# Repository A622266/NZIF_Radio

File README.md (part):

# NZIF Radio

Near-zero-IF radio architecture built around an 8-phase harmonic rejection polyphase mixer and audio-rate ADC/DAC signal processing.

This board is the NZIF core: it converts differential RF into low-frequency quadrature baseband, then digitizes and processes the result with audio-rate converters and a SigmaDSP. The RF front-end board handles the PA, T/R switch, a band-switched quasi-elliptic LPF bank shared between TX and RX, a directional coupler for SWR and power measurement at the antenna port, and two receive-path high-pass filters that together form a band-specific preselector. The receive and transmit mixer/baseband cores are on this board.

## Design goals

- Suppress the 3rd, 5th, and 7th LO harmonics with an 8-phase harmonic rejection mixer, reducing reliance on RF bandpass filters on this board.
- Use polyphase mixing and phase-domain harmonic suppression to minimize analog RF selectivity requirements.
- Avoid a conventional high-IF architecture: the design is near-zero-IF, using 192 kHz ADC/DAC sampling with a digital NCO offset to stay away from DC and 1/f noise.
- Keep the Rx and Tx front end compact and fully differential, while placing the PA and post-PA filters on a separate board.
- Preserve differential signal flow from the RF mixer through the driver amps and into the audio-rate converters.
- Share a quasi-elliptic post-PA LPF bank between TX and RX on the RF front-end board: on transmit it suppresses PA harmonics for regulatory compliance; on receive the same bank acts as a band-specific preselector with deep notch traps at adjacent-band interference sources.
- Place a directional coupler at the antenna interface (after the LPF bank) for accurate forward/reflected power and SWR measurement at the clean fundamental; use a calibration tap to inject a spectrally clean reference tone into the receive path for I/Q calibration.
- Apply strategically placed high-pass filters in the receive chain: a fixed ~1.6 MHz filter to block AM broadcast on all bands, and a switched ~9 MHz filter to suppress lower-band interference on 30m and above.

## Architecture overview

### Core concept

The NZIF board uses an 8-phase commutating mixer topology on receive and transmit. In the receive path, differential RF (`RF+`, `RF-`) is sampled by eight phase-shifted switch networks, producing eight baseband phase taps. Opposite phases are then recombined into four differential channels for ADC conversion:

- `BB_0` / `BB_180` → `P0_IN+` / `P0_IN-`
- `BB_45` / `BB_225` → `P45_IN+` / `P45_IN-`
- `BB_90` / `BB_270` → `P90_IN+` / `P90_IN-`
- `BB_135` / `BB_315` → `P135_IN+` / `P135_IN-`

The eight-phase approach provides phase-domain cancellation of odd-order LO harmonics (3rd, 5th, 7th) and reduces the need for RF bandpass filtering on this board.

### Near-zero-IF operation

This is not a classic zero-IF design:

- ADC and DAC converters run at 192 kHz.
- The ADAU1467 DSP uses a digital NCO to shift the effective center frequency away from DC.
- That offset avoids LO leakage and 1/f noise while preserving complex I/Q demodulation.

Because the converters are audio-rate, the RF conversion chain moves entirely into the phase-domain mixer and the digital domain — there is no IF filter bank.

## How the receive signal flows

```
Antenna → Directional coupler (~0.2 dB through) → ZWAS LPF bank (band-switched preselector)
    → T/R switch → HP-1 (~1.6 MHz, fixed) → HP-2 (~9 MHz, switched 30m+)
    → SMA (J101) → 1:1 balun → RF+ / RF-
    → SN74CBT3125C quad switch arrays (×4)
        controlled by phase_0, phase_45, … phase_315
        ├─ BB_0    → ADA4625-2 unity-gain buffer
        ├─ BB_45   → ADA4625-2 unity-gain buffer
        ├─ BB_90   → ADA4625-2 unity-gain buffer
        ├─ BB_135  → ADA4625-2 unity-gain buffer
        ├─ BB_180  → ADA4625-2 unity-gain buffer
        ├─ BB_225  → ADA4625-2 unity-gain buffer
        ├─ BB_270  → ADA4625-2 unity-gain buffer
        └─ BB_315  → ADA4625-2 unity-gain buffer
    → top sheet pairs opposite phases into differential channels:
        BB_0/BB_180   → P0_IN+/P0_IN-
        BB_45/BB_225  → P45_IN+/P45_IN-
        BB_90/BB_270  → P90_IN+/P90_IN-
        BB_135/BB_315 → P135_IN+/P135_IN-
    → ADA4945-1 fully differential amplifiers (×4)
        → P0_FDA+/P0_FDA-, P45_FDA+/P45_FDA-,
          P90_FDA+/P90_FDA-, P135_FDA+/P135_FDA-
    → ADAU1979 4-channel 24-bit ADC (192 kHz)
    → ADAU1467 SigmaDSP: I/Q correction, NCO offset, filter, demodulate
    → ADAU1361 audio codec → headphone/speaker
```

## How the transmit signal flows

```
Mic → ADAU1361 ADC → ADAU1467 DSP (Weaver SSB / CW shaping)
    → ADAU1962A 12-ch DAC (I/Q baseband, 192 kHz)
    → SN74CBTLV3125 switch arrays
        driven by same phase_0 … phase_315 clock lines
    → 8-phase RF reconstruction → RF output
    → RF front-end board: pre-driver → PA → T/R switch
    → ZWAS quasi-elliptic LPF bank (7 filters, harmonic rejection)
    → Directional coupler → antenna
        ├─ Fwd port → detector → Pi Pico ADC (forward power / SWR)
        ├─ Rev port → detector → Pi Pico ADC (reflected power / SWR)
        └─ Tap → HMC1118 → RX path (I/Q calibration reference)
```

## What is on this board

### `nzif/rx_mixer.kicad_sch`

Implements the receive 8-phase polyphase mixer.

- Four **SN74CBT3125CPW** quad bus-switch ICs commutate the differential RF input (`RF+`/`RF-`) onto eight phase-tagged baseband nodes. Two switch ICs handle the `RF+` half of the differential signal; two handle `RF-`. The eight phase-control lines (`phase_0`, `phase_45`, … `phase_315`) are driven from the clock tree.
- Each baseband node is buffered by one section of an **ADA4625-2** unity-gain op-amp. The ADA4625-2 is a dual JFET-input op-amp (3.3 nV/√Hz input noise, rail-to-rail output) that isolates the high-impedance switch nodes from the downstream differential signal chain and prevents charge injection from disturbing adjacent phase taps.

### `nzif/rx_driver_amps.kicad_sch`

Converts the eight single-ended phase outputs into four differential channels for the ADC.

- Four **ADA4945-1** fully differential amplifiers condition the signals. Each ADA4945-1 takes a pair of opposite-phase single-ended inputs and produces a differential output directly suitable for the ADAU1979 differential input. Gain is set by the Rf/Rg resistor network on each channel.
- Outputs: `P0_FDA+/P0_FDA-`, `P45_FDA+/P45_FDA-`, `P90_FDA+/P90_FDA-`, `P135_FDA+/P135_FDA-`.

### `nzif/adcs.kicad_sch`

- Contains the **ADAU1979** 4-channel 24-bit audio ADC.
- Digitizes the four differential baseband pairs at 192 kHz.
- The ADAU1979 is chosen for its 4.5 Vrms differential input range, which provides headroom against strong-signal transients before any AGC correction occurs.

### `nzif/dacs.kicad_sch`

- Contains the **ADAU1962A** 12-channel 24-bit audio DAC.
- Generates the analog transmit I/Q channels for the TX mixer at 192 kHz.
- The 12-channel output provides multiple differential pairs for the TX baseband; the same I2S/TDM protocol used by the ADAU1979 connects directly to the ADAU1467.

### `nzif/tx_mixer.kicad_sch`

- Implements the transmit 8-phase RF reconstruction mixer.
- Uses **SN74CBTLV3125** bus-switch arrays (the 3.3 V-rated LV variant, matched to DAC output levels) to commutate the I/Q baseband onto the 8-phase RF reconstruction network.
- Uses the same `phase_0` … `phase_315` control lines as the receive mixer.

### `nzif/dsp.kicad_sch`

- Contains the **ADAU1467** SigmaDSP (dual-core, 294 MHz).
- Programmed via SigmaStudio (graphical block-diagram, no traditional firmware).
- Receive functions: I/Q DC offset correction, gain and phase trim, NCO fine-tuning (±96 kHz), digital FIR/IIR selectivity filtering, AGC, SSB/CW/AM demodulation (Weaver method).
- Transmit functions: Weaver SSB encoding, CW keying-envelope shaping, TX I/Q baseband generation.
- The Pi Pico writes calibration coefficients and NCO frequency words to ADAU1467 parameter RAM over I2C.

### `nzif/clock_tree.kicad_sch`

Generates the LO and the eight phase-control signals for both the Rx and Tx mixers.

- **AD9523-1** clock generator provides both the RF LO and the system audio MCLK from a single on-chip VCO. The VCO-path outputs drive the phase distribution logic; a separate reference-path output provides a stable fixed MCLK to all audio ICs, completely independent of LO tuning.
- **CTS_535_TCXO** provides the precision reference clock for the AD9523-1 PLL.
- **SN74AUC16374** (16-bit D flip-flop, 2.5V supply) is wired as two independent 8-stage ring counters — one for Rx and one for Tx, using the IC's two independent 8-bit banks. Each counter is a shift-register loop: D2=Q1, D3=Q2, …, D8=Q7, with Q8 (8-phase) or Q4 (4-phase) fed back to D1. A single '1' circulating through the active stages produces the non-overlapping phase pulses that drive the mixer switches.
- **SN74AUC08** quad AND gates (one IC per counter, 2.5V supply) gate the D5–D8 shift connections. When `PHASE_SEL_8` is high, all 8 stages circulate normally (8-phase mode). When `PHASE_SEL_8` is low, D5–D8 are forced to zero, quenching stages 5–8 so only a 4-stage ring (Q1–Q4) remains active (4-phase mode).
- **SN74CBTLV3253** dual 4:1 analog mux (2.5V supply, U705=Rx, U706=Tx) selects both the D1 data input and the counter clock on each band change and during initialisation. The Pico drives S0/S1 (`RX_UC_ADDR0/1`, `TX_UC_ADDR0/1`) to choose one of four modes:

  | S1:S0 | D1 source | Clock source | Purpose |
  |-------|-----------|--------------|---------|
  | 0,0 | GND | `init_clock` (Pico GPIO) | Clear — flush 0s through all stages |
  | 0,1 | 2.5V | `init_clock` | Seed — inject one '1' into D1 |
  | 1,0 | Q4 (`counter_feedback_4`) | `high_speed_clock` (AD9523-1) | 4-phase run (6m band) |
  | 1,1 | Q8 (`counter_feedback_8`) | `high_speed_clock` | 8-phase run (160m–10m) |

- **SN74LVC8T245** dual-supply level translators (U704=Rx, U707=Tx, VCC_A=2.5V, VCC_B=3.3V) convert the 2.5V ring counter Q outputs to the 3.3V levels required by the mixer bus switches, producing `rx_phase_0`…`rx_phase_315` and `tx_phase_0`…`tx_phase_315`.
- **`PHASE_SEL_8`** (Pico GPIO at 3.3V) is divided to ~2.5V by R1226 (10 kΩ series) and R1227 (33 kΩ to GND) before reaching the AUC08 AND gate inputs, keeping the signal within the AUC08 absolute-maximum input of VCC+0.5V = 3.0V at its 2.5V supply.

### `nzif/microcontroller.kicad_sch`

- Contains a **Raspberry Pi Pico** (RP2040, dual-core Arm Cortex-M0+, 133 MHz, 264 kB SRAM, 2 MB flash).
- Controls frequency tuning (programs the AD9523-1 via SPI), manages band changes, runs the I/Q calibration routine, handles front-panel input (rotary encoder, buttons, display), and presents a Hamlib-compatible UART CAT port for logging software.

### `nzif/audio_subsystem.kicad_sch`

- Contains the **ADAU1361** stereo audio codec.
- On receive: DAC output drives headphone/speaker with demodulated audio from the ADAU1467.
- On transmit: ADC input digitizes the microphone and feeds the ADAU1467 DSP.

### `nzif/power_ldos.kicad_sch`

- **LT3045** ultra-low-noise positive LDO (2 μVrms) for precision analog and RF rails.
- **LT3094** ultra-low-noise negative LDO for the bipolar op-amp supply rails.
- LDO choice is driven by the ADC noise floor and LO phase noise — both track supply noise on the precision analog rails.

### `nzif/power_switching_reg.kicad_sch`

- **LT8330** boost converter and **ADP2302/ADP2303** switching regulators for digital rails.

## RF front-end board

The RF front-end board sits between the antenna and the NZIF core and contains all antenna-interface, preselector, PA, and power-measurement functions. It implements the same front-end architecture used in a companion HF superheterodyne transceiver — both designs share this topology at the antenna interface.

### T/R switch

Fast RF switch routing the antenna between receive and transmit paths. Low insertion loss (< 0.3 dB); fast enough for break-in CW operation.

### HP-1 (~1.6 MHz, fixed, receive path only)

Always-in high-pass filter immediately after the T/R switch in the receive path. Blocks AM broadcast (0.535–1.705 MHz), which otherwise passes even through the widest ZWAS LPF (LPF-1 at 2.5 MHz cutoff). Not in the TX path.

### HP-2 (~9 MHz, switched, receive path only)

Pi Pico activates this filter on 30m and above. Rejects 40m (7–7.3 MHz), 80m, and 160m interference when operating on higher bands. At a 9 MHz cutoff, the 40m band edge (7.3 MHz = 0.81× the cutoff) sees 30–40 dB rejection from a 7-pole LC high-pass filter; the 30m band (10.1 MHz = 1.12× the cutoff) passes with < 0.3 dB insertion loss. Together with the ZWAS LP filter, HP-2 creates an effective two-sided passband window (9 MHz to the ZWAS LP cutoff) on 30m and above without requiring a switched bandpass filter bank. Not in the TX path.

### ZWAS quasi-elliptic LPF bank (dual-purpose, shared TX/RX)

Seven switched quasi-elliptic low-pass filters using the Tonne/Elsie ZWAS technique. Each filter is a Chebyshev LPF with one shunt LC trap at the 2nd harmonic of the band group's highest frequency. Pi Pico selects the correct filter by band; the same selection serves TX and RX.

**On transmit:** The trap provides deep notch rejection of the 2nd PA harmonic for regulatory compliance. The LP rolloff handles higher-order harmonics. Together they meet FCC Part 97 spurious emission requirements at 100 W output.

**On receive:** The same trap falls at exactly the next adjacent amateur band up — the most common strong-signal interference source — providing a deep notch preselector. The 80m LPF traps 40m; the 40m LPF traps 20m; and so on.

| Filter | Bands | LP cutoff | ZWAS trap | TX: 2nd harmonic rejected | RX: adjacent-band trap |
|--------|-------|-----------|-----------|--------------------------|------------------------|
| LPF-1 | 160m | 2.5 MHz | 3.6 MHz | 2× 1.8 MHz = 3.6 MHz ✓ | 80m lower edge (near trap) |
| LPF-2 | 80m | 5.0 MHz | 7.0 MHz | 2× 3.5 MHz = 7.0 MHz ✓ | **40m — deep notch** |
| LPF-3 | 40m | 9.0 MHz | 14.0 MHz | 2× 7.0 MHz = 14.0 MHz ✓ | **20m — deep notch** |
| LPF-4 | 30m, 20m | 16 MHz | 28.0 MHz | 2× 14 MHz = 28 MHz ✓ | 10m |
| LPF-5 | 17m, 15m | 22 MHz | 36 MHz | 2× 18 MHz = 36 MHz ✓ | 12m/10m edge |
| LPF-6 | 12m, 10m | 32 MHz | 50 MHz | 2× 25 MHz = 50 MHz ✓ | 6m — deep notch |
| LPF-7 | 6m | 60 MHz | 108 MHz | 2× 54 MHz = 108 MHz ✓ | FM broadcast (88–108 MHz) |

### Directional coupler

Dual-transformer design positioned between the ZWAS LPF bank and the antenna, where the signal is a clean fundamental with harmonics already suppressed at a defined 50 Ω interface. Present in both TX and RX paths; through-path insertion loss ~0.2 dB on receive.

- **Forward port**: Coupled to a Schottky diode peak detector; DC output drives a Pi Pico ADC input for forward power measurement.
- **Reflected port**: Coupled to a second Schottky diode peak detector; DC output drives a Pi Pico ADC input for reflected power and SWR display. Fold-back protection is implemented in Pi Pico firmware.
- **Calibration tap**: A third coupled port samples the transmitted signal at low level. An HMC1118 switch routes this tap into the NZIF receive path for I/Q calibration — the tone has already passed through the ZWAS LPF, so it is spectrally clean and within the operating band.

### Effective receive preselector passband (HP-1 + HP-2 + ZWAS)

| Band | HP-2 | ZWAS filter | Effective window | Key rejections |
|------|------|-------------|-----------------|----------------|
| 160m | Bypass | LPF-1: 2.5 MHz / trap 3.6 MHz | 1.6–2.5 MHz | 80m (near trap + rolloff), all above |
| 80m | Bypass | LPF-2: 5.0 MHz / trap 7.0 MHz | 1.6–5.0 MHz | **40m deep notch**, all above |
| 60m | Bypass | LPF-3: 9.0 MHz / trap 14.0 MHz | 1.6–9.0 MHz | 20m deep notch, 30m rolloff |
| 40m | Bypass | LPF-3: 9.0 MHz / trap 14.0 MHz | 1.6–9.0 MHz | **20m deep notch**, 30m rolloff |
| 30m | In (9 MHz) | LPF-4: 16 MHz / trap 28.0 MHz | **9–16 MHz** | 40m (30–40 dB), 80m/160m; 10m trap |
| 20m | In (9 MHz) | LPF-4: 16 MHz / trap 28.0 MHz | **9–16 MHz** | 40m (30–40 dB), 80m/160m; 10m trap |
| 17m | In (9 MHz) | LPF-5: 22 MHz / trap 36 MHz | **9–22 MHz** | 40m, SW broadcast, 80m/160m; 12m/10m trap |
| 15m | In (9 MHz) | LPF-5: 22 MHz / trap 36 MHz | **9–22 MHz** | Same as 17m |
| 12m | In (9 MHz) | LPF-6: 32 MHz / trap 50 MHz | **9–32 MHz** | 40m, SW, 20m; 6m trap |
| 10m | In (9 MHz) | LPF-6: 32 MHz / trap 50 MHz | **9–32 MHz** | Same as 12m |
| 6m | In (9 MHz) | LPF-7: 60 MHz / trap 108 MHz | **9–60 MHz** | 40m, SW broadcast, FM broadcast trap |

## LO chain

```
CTS_535_TCXO → AD9523-1 PLL → LO output   (VCO path → SN74AUC16374 ring counters (2.5V)
                                             → SN74AUC08 AND gates (phase-mode select)
                                             → SN74CBTLV3253 init/run mux
                                             → SN74LVC8T245 level shifters (2.5V → 3.3V)
                                             → phase_0 … phase_315 → mixer switch gates)
                            → MCLK output  (reference path, fixed ~12.288 MHz
                                             → ADAU1979, ADAU1467, ADAU1962A, ADAU1361)
```

The AD9523-1 VCO is tuned by the Pi Pico (via SPI) to the operating frequency. The reference-path MCLK output is completely decoupled from VCO tuning, so retuning the LO does not disturb the audio clock.

### Ring counter initialisation

The SN74AUC16374 ring counters can power up in any state. Before the mixers are enabled on every power-up and band change, the Pico runs the following sequence using the 3253 mux and a slow `init_clock` GPIO:

1. **Clear** (S=00, 9+ `init_clock` pulses): D1=GND; clocks 0s through all 8 stages, flushing any spurious bit patterns.
2. **Seed** (S=01, 1 `init_clock` pulse): D1=2.5V; loads a single '1' into Q1 with all other stages already 0.
3. **Set phase mode**: assert `PHASE_SEL_8` high (8-phase) or low (4-phase). The AND gates latch the D5–D8 gating before the high-speed clock starts.
4. **Run** (S=10 for 4-phase, S=11 for 8-phase): switches D1 to the Q4 or Q8 feedback net and the clock source to `high_speed_clock` from the AD9523-1. The single '1' circulates freely at LO rate.

The `init_clock` is a Pico GPIO toggled in firmware at a few kHz — well below any setup/hold concern. `PHASE_SEL_8` must be asserted before switching S to the run state so that stages 5–8 are quenched before Q4 feedback is engaged in 4-phase mode.

### 8-phase vs 4-phase mode

| Parameter | 8-phase (160m–10m) | 4-phase (6m) |
|-----------|-------------------|--------------|
| AD9523-1 output divider | ÷8, clock = 8× RF | ÷4, clock = 4× RF |
| Active ring stages | 8 (Q1–Q8) | 4 (Q1–Q4) |
| `PHASE_SEL_8` / D5–D8 | High — pass Q4–Q7 | Low — forced 0 |
| Counter feedback to D1 | Q8 | Q4 |
| Phase pulse width | 45° (1/8 RF period) | 90° (1/4 RF period) |
| Maximum counter clock | ~240 MHz (at 30 MHz RF, 10m) | 216 MHz (at 54 MHz RF, 6m) |
| Odd harmonic cancellation | 3rd, 5th, and 7th cancelled by DSP combining | 3rd and 7th cancelled; 5th passes |

The SN74AUC16374 is rated to a maximum VCC of 2.7V, operated here at 2.5V. At 8× RF for 10m the counter clock reaches ~240 MHz; for 6m, 8-phase would require 400–432 MHz which exceeds the device rating. Switching to 4-phase keeps the clock at ≤216 MHz with margin.

In 8-phase mode the four differential ADC channels (each formed by pairing a phase tap with its 180°-opposite) have linearly independent response vectors for k=1, 3, 5, and 7 — they are distinct rows of the 8-point DFT matrix. The ADAU1467 DSP applies complex combining weights that simultaneously pass the fundamental while zeroing all three harmonic responses. The first unrejected harmonic is the 9th (response to signals at f_LO/9), which falls far outside any amateur band for HF frequencies.

In 4-phase mode (6m) the active taps are only at 0°, 90°, 180°, 270° (Q5–Q8 are quenched). Because the tap spacing is 90°, the 5th harmonic produces the same response vector as the fundamental [1, j, −1, −j], making them indistinguishable. The 3rd and 7th harmonics share the orthogonal vector [1, −j, −1, j] and are both cancelled together. The practical consequence on 6m is a spurious response to signals at f_LO/5 ≈ 10–10.8 MHz (30m band). The HP-2 filter (9 MHz cutoff, active on 6m) provides only modest attenuation at 10 MHz, so strong 30m signals can create interference on 6m in 4-phase mode.

## Why 8-phase harmonic rejection?

A conventional 2-phase (single-switch) commutating mixer has a square-wave LO that contains odd harmonics. The 3rd harmonic at −9.5 dBc (amplitude ratio 1/3) causes a mixing response to signals at f_RF/3 — an unwanted reception at 1/3 of the operating frequency, suppressed only by external bandpass filtering.

The 8-phase architecture cancels these harmonics by phase. Each of the eight switch taps samples the RF with a LO phase that is an integer multiple of 45°. When the eight outputs are recombined, the harmonic responses cancel as rotating phasor sums:

- **3rd harmonic:** each tap's 3rd-harmonic component is phase-shifted by 3 × 45° = 135° relative to adjacent taps. Summing eight equal phasors separated by 135° gives a vector sum of zero. Theoretical rejection: >60 dB.
- **5th harmonic:** 5 × 45° = 225° per step; vector sum ≈ 0. Theoretical rejection: >50 dB.
- **7th harmonic:** 7 × 45° = 315° per step; vector sum ≈ 0. Theoretical rejection: >45 dB.

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
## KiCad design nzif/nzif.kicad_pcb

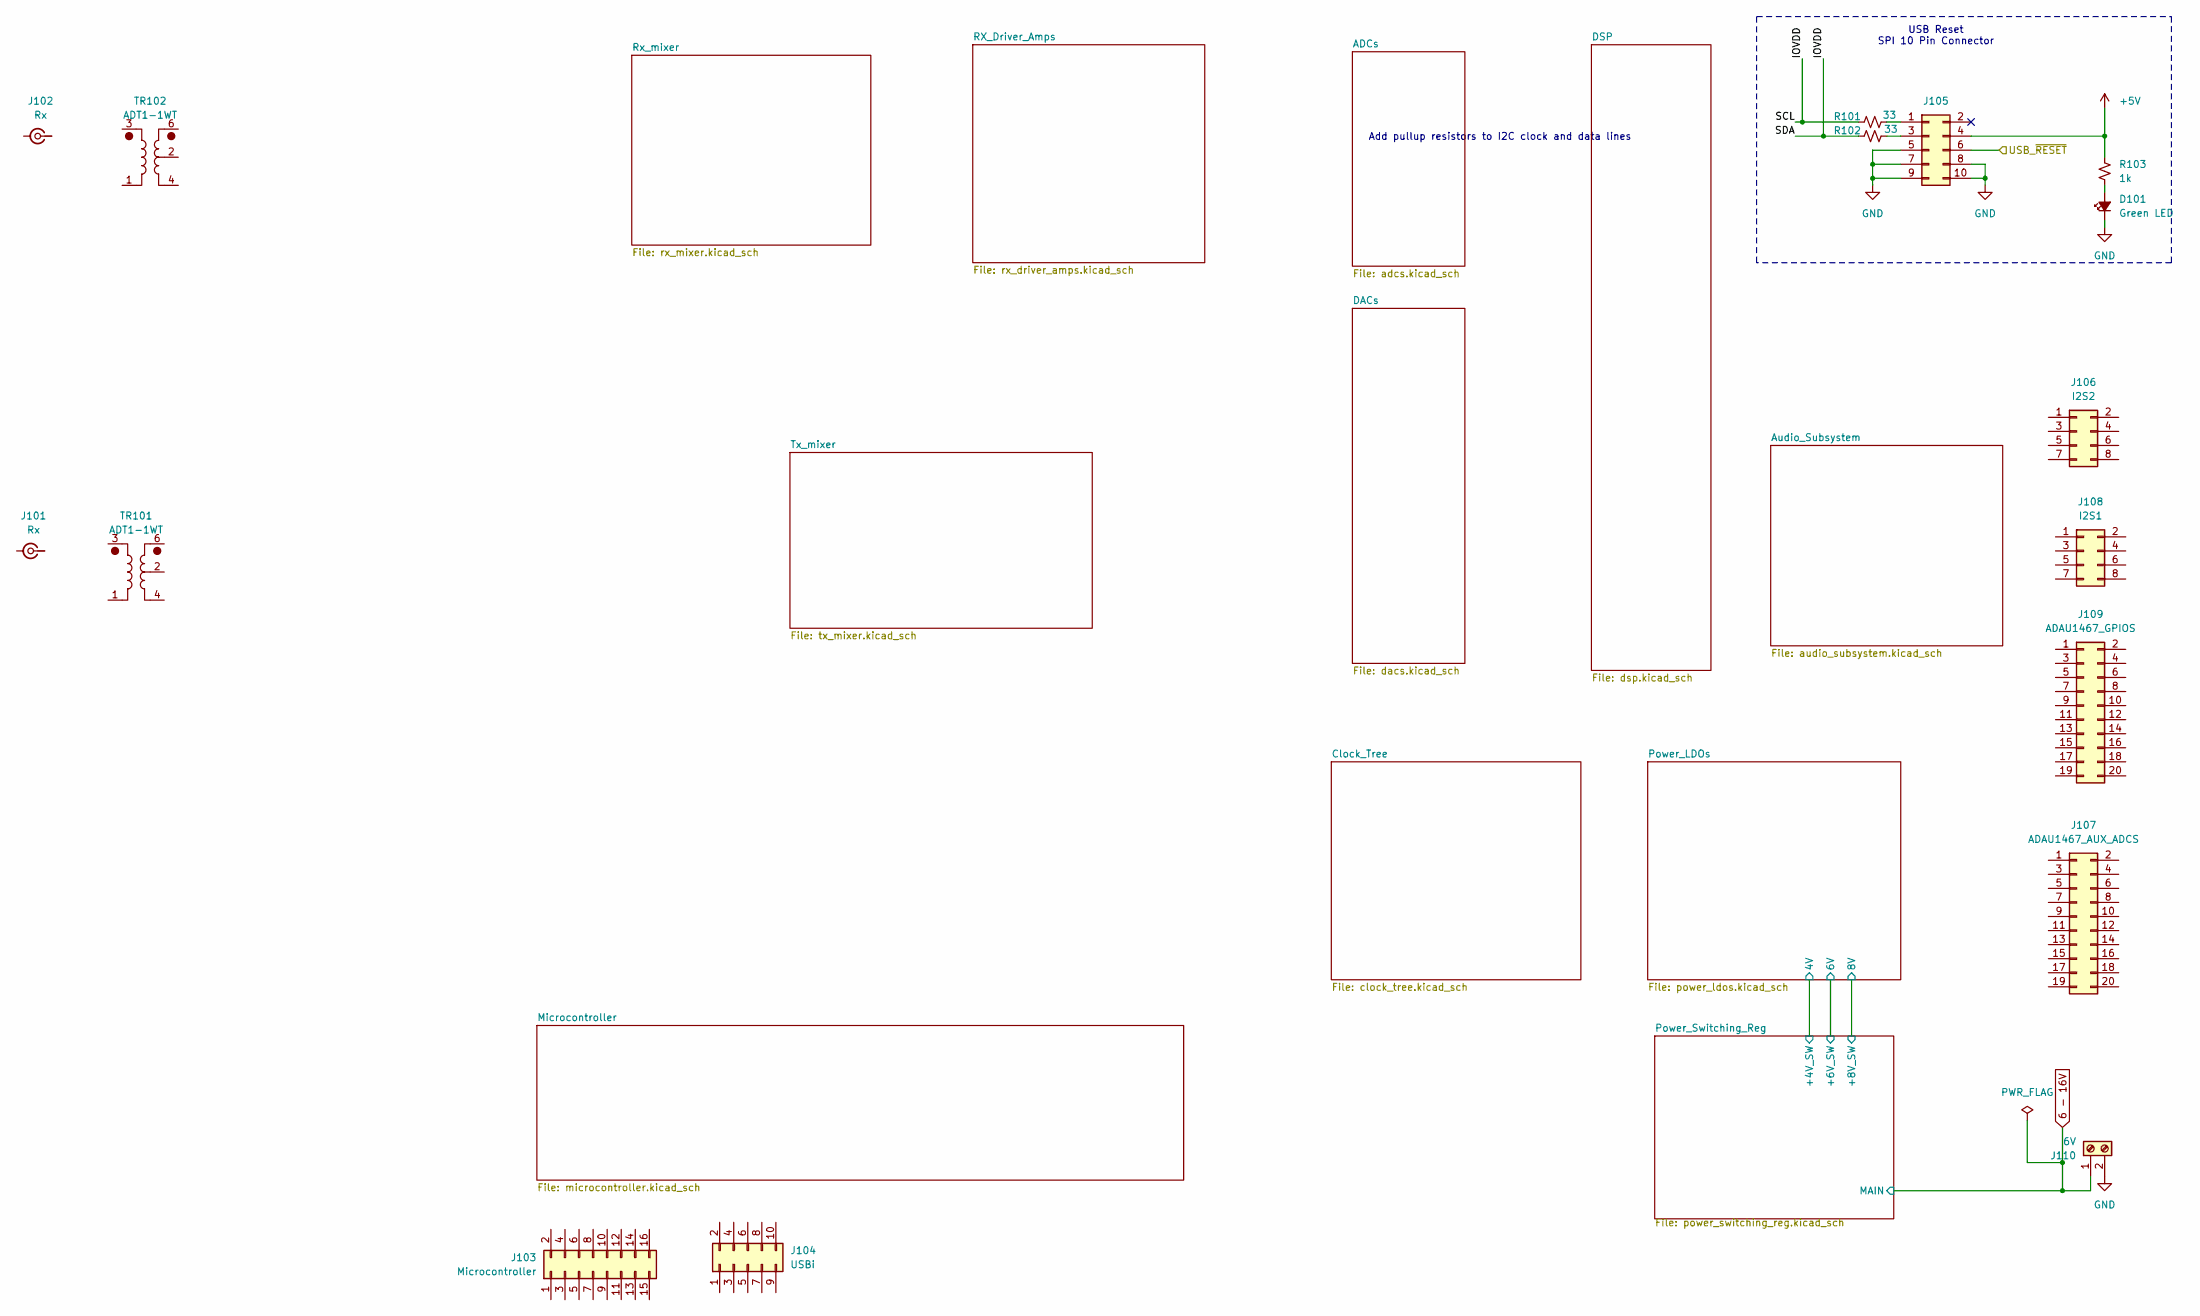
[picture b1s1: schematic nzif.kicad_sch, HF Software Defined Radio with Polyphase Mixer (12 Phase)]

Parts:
D101: Green LED
J101, J102: Rx
J103: Microcontroller
J104: USBi
J105: Conn_02x05_Odd_Even
J106: I2S2
J107: ADAU1467_AUX_ADCS
J108: I2S1
J109: ADAU1467_GPIOS
J110: 6V
R101, R102: 33
R103: 1k
TR101, TR102: ADT1-1WT; Mini-Circuits_CD542_H2.84mm

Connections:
/6_-_16V: J110.1; also elsewhere on the board
/DAC_CM_1.5V: TR102.2; also elsewhere on the board
/RF-In: J101.1 (In), TR101.3
/Rx_mixer/RF+: TR101.6; also elsewhere on the board
/Rx_mixer/RF-: TR101.4; also elsewhere on the board
/TX-out: J102.1 (In), TR102.3
/Tx_mixer/TX_RF+: TR102.6; also elsewhere on the board
/Tx_mixer/TX_RF-: TR102.4; also elsewhere on the board
unnamed 283: J101.2 (Ext); also elsewhere on the board
unnamed 284: J102.2 (Ext); also elsewhere on the board
unnamed 310: D101.2 (A), R103.2; also elsewhere on the board
unnamed: J105.4, R103.1

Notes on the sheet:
Add pullup resistors to I2C clock and data lines
USB Reset SPI 10 Pin Connector

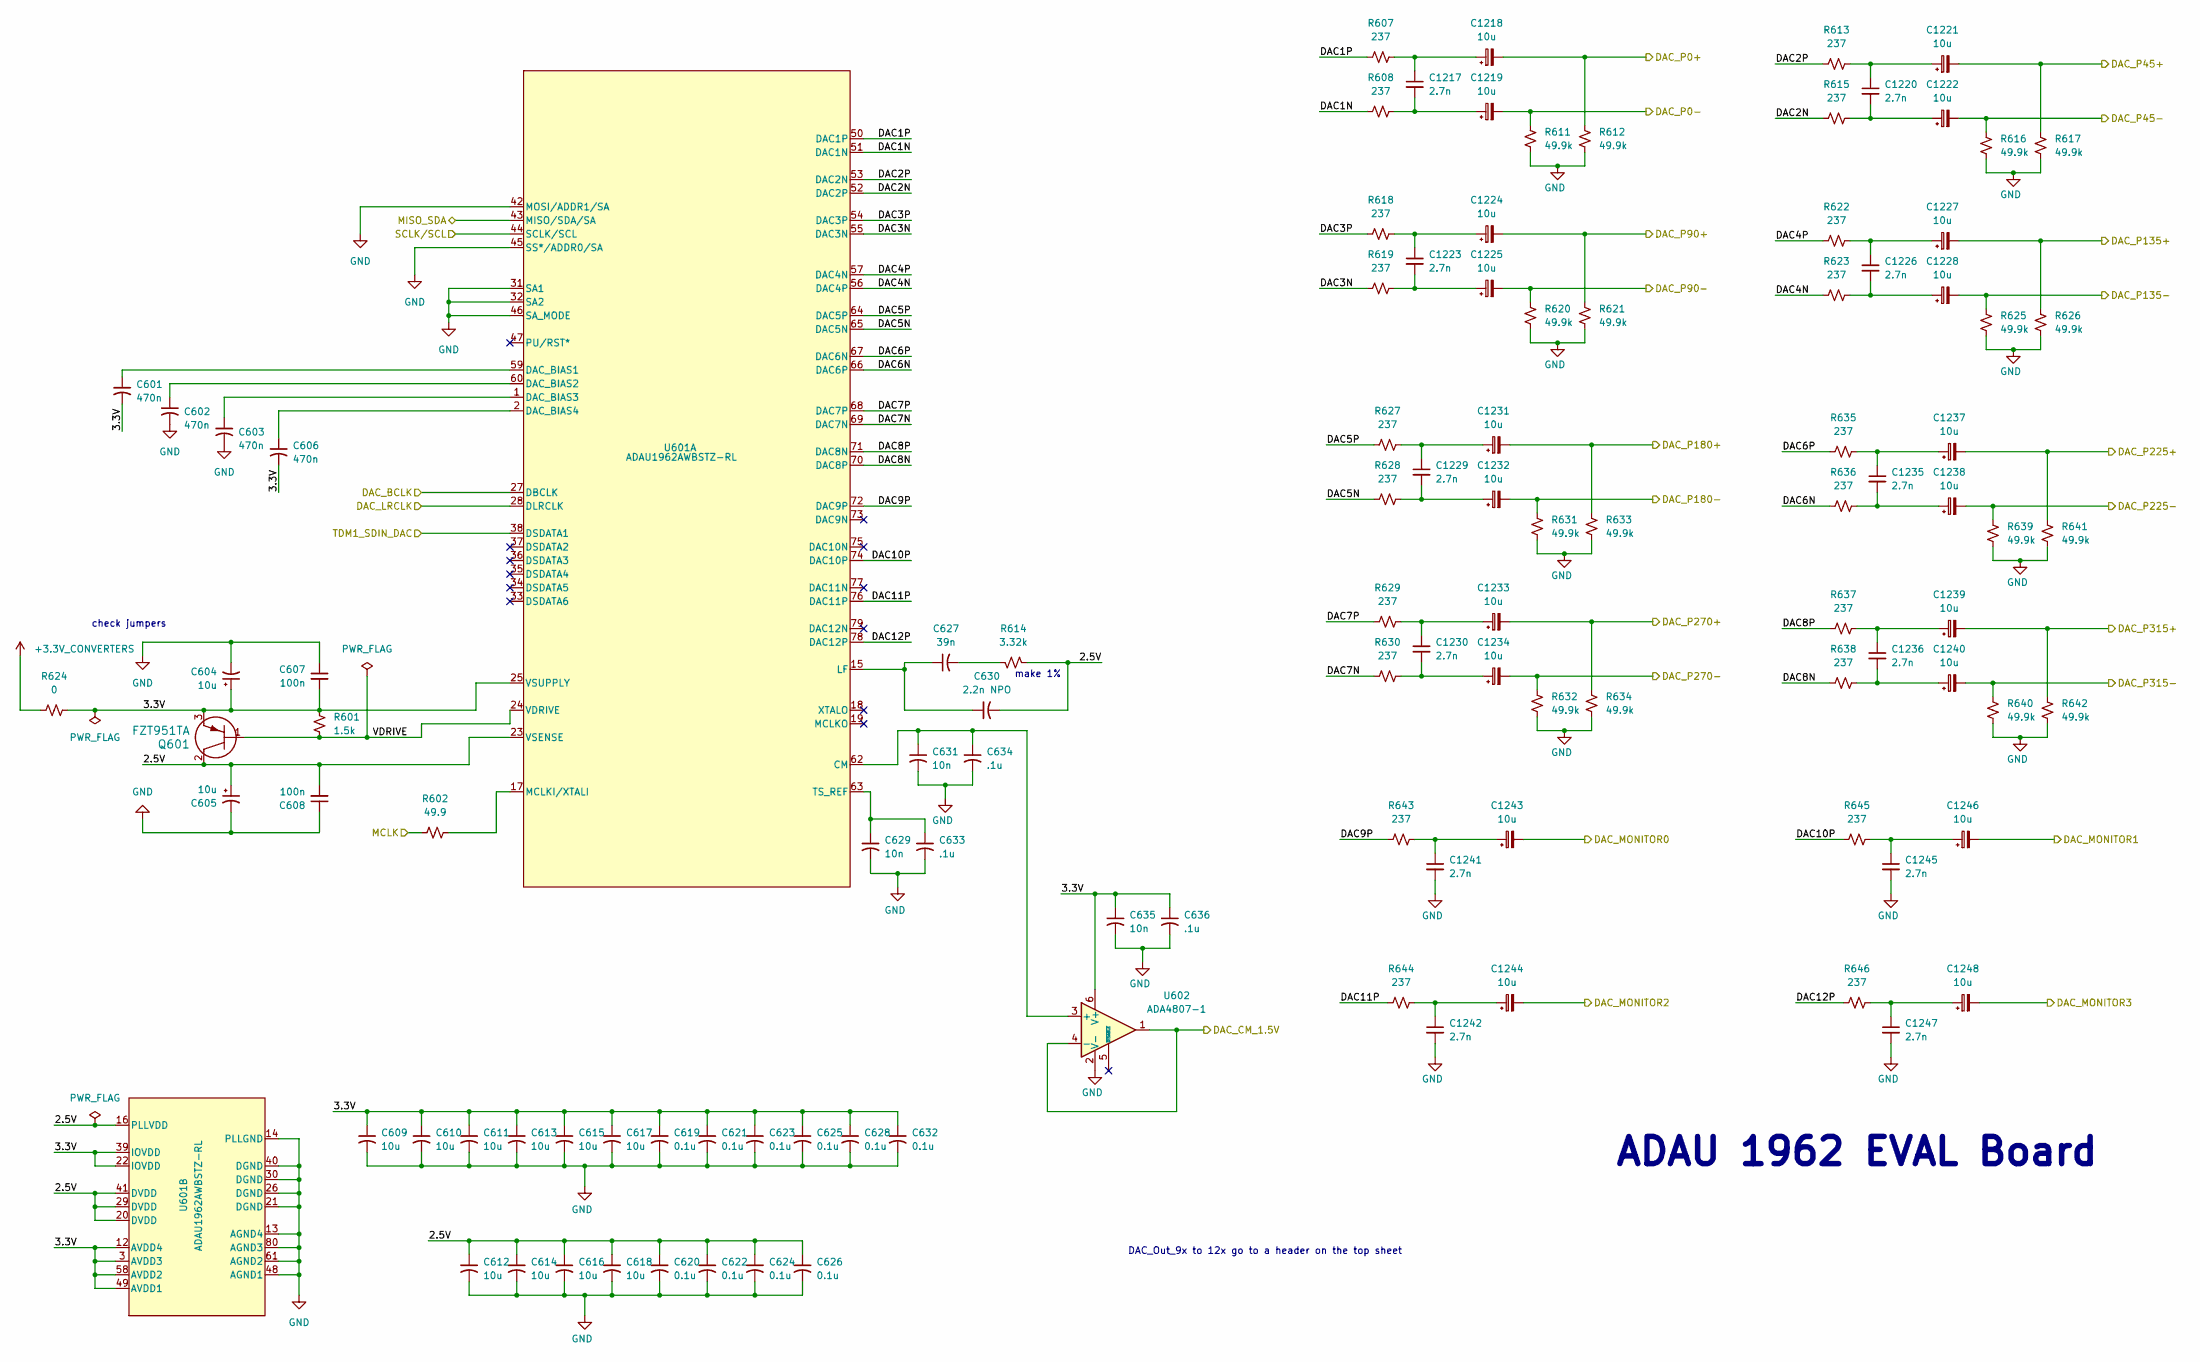
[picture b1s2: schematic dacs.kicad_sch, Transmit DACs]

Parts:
C601, C602, C603, C606: 470n; C_0402_1005Metric_Pad0.74x0.62mm_HandSolder
C604, C605, C609, C610, C611, C612, C613, C614, C615, C616, C617, C618: 10u; C_0402_1005Metric_Pad0.74x0.62mm_HandSolder
C607, C608: 100n; C_0402_1005Metric_Pad0.74x0.62mm_HandSolder
C619, C620, C621, C622, C623, C624, C625, C626, C628, C632: 0.1u; C_0402_1005Metric_Pad0.74x0.62mm_HandSolder
C627: 39n; C_0402_1005Metric_Pad0.74x0.62mm_HandSolder
C629, C631, C635: 10n; C_0402_1005Metric_Pad0.74x0.62mm_HandSolder
C630: 2.2n NPO; C_0402_1005Metric_Pad0.74x0.62mm_HandSolder
C633, C634, C636: .1u; C_0402_1005Metric_Pad0.74x0.62mm_HandSolder
C1217, C1220, C1223, C1226, C1229, C1230, C1241, C1242, C1245, C1247: 2.7n; C_0402_1005Metric_Pad0.74x0.62mm_HandSolder
C1218, C1219, C1221, C1222, C1224, C1225, C1227, C1228, C1231, C1232, C1233, C1234, C1237, C1238, C1239, C1240, C1243, C1244, C1246, C1248: 10u; CP_Elec_4x4.5
C1235, C1236: 2.7n; CP_Elec_4x4.5
Q601: FZT951TA; SOT223-FZT690B-DN_DIO
R601: 1.5k; R_0402_1005Metric_Pad0.72x0.64mm_HandSolder
R602: 49.9; R_0402_1005Metric_Pad0.72x0.64mm_HandSolder
R607, R608, R613, R615, R618, R619, R622, R623, R627, R628, R629, R630, R635, R636, R637, R638, R643, R644, R645, R646: 237; R_0402_1005Metric_Pad0.72x0.64mm_HandSolder
R611, R612, R616, R617, R620, R621, R625, R626, R631, R632, R633, R634, R639, R640, R641, R642: 49.9k; R_0402_1005Metric_Pad0.72x0.64mm_HandSolder
R614: 3.32k; R_0402_1005Metric_Pad0.72x0.64mm_HandSolder
R624: 0; R_0402_1005Metric_Pad0.72x0.64mm_HandSolder
U601: ADAU1962AWBSTZ-RL; ST_80_2_ADI
U602: ADA4807-1; SOT-23-6

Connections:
+3.3V_CONVERTERS: R624.1; also elsewhere on the board
/DAC_CLK: R602.1; also elsewhere on the board
/DAC_CM_1.5V: U602.1, U602.4 (-); also elsewhere on the board
/DACs/2.5V: C605.1, C608.2, C612.1, C614.1, C616.1, C618.1, C620.1, C622.1, C624.1, C626.1, C630.2, Q601.2, R614.2, U601.16 (PLLVDD), U601.20 (DVDD), U601.23 (VSENSE), U601.29 (DVDD), U601.41 (DVDD)
/DACs/3.3V: C601.2, C604.1, C606.2, C607.2, C609.1, C610.1, C611.1, C613.1, C615.1, C617.1, C619.1, C621.1, C623.1, C625.1, C628.1, C632.1, C635.1, C636.1, Q601.3, R601.1, R624.2, U601.3 (AVDD3), U601.12 (AVDD4), U601.22 (IOVDD), U601.25 (VSUPPLY), U601.39 (IOVDD), U601.49 (AVDD1), U601.58 (AVDD2), U602.6 (V+)
/DACs/DAC1N: R608.1, U601.51 (DAC1N)
/DACs/DAC1P: R607.1, U601.50 (DAC1P)
/DACs/DAC2N: R615.1, U601.52 (DAC2P)
/DACs/DAC2P: R613.1, U601.53 (DAC2N)
/DACs/DAC3N: R619.1, U601.55 (DAC3N)
/DACs/DAC3P: R618.1, U601.54 (DAC3P)
/DACs/DAC4N: R623.1, U601.56 (DAC4P)
/DACs/DAC4P: R622.1, U601.57 (DAC4N)
/DACs/DAC5N: R628.1, U601.65 (DAC5N)
/DACs/DAC5P: R627.1, U601.64 (DAC5P)
/DACs/DAC6N: R636.1, U601.66 (DAC6P)
/DACs/DAC6P: R635.1, U601.67 (DAC6N)
/DACs/DAC7N: R630.1, U601.69 (DAC7N)
/DACs/DAC7P: R629.1, U601.68 (DAC7P)
/DACs/DAC8N: R638.1, U601.70 (DAC8P)
/DACs/DAC8P: R637.1, U601.71 (DAC8N)
/DACs/DAC9P: R643.1, U601.72 (DAC9P)
/DACs/DAC10P: R645.1, U601.74 (DAC10P)
/DACs/DAC11P: R644.1, U601.76 (DAC11P)
/DACs/DAC12P: R646.1, U601.78 (DAC12P)
/DACs/DAC_BCLK: U601.27 (DBCLK); also elsewhere on the board
/DACs/DAC_LRCLK: U601.28 (DLRCLK); also elsewhere on the board
/DACs/DAC_MONITOR0: C1243.2; also elsewhere on the board
/DACs/DAC_MONITOR1: C1246.2; also elsewhere on the board
/DACs/DAC_MONITOR2: C1244.2; also elsewhere on the board
/DACs/DAC_MONITOR3: C1248.2; also elsewhere on the board
/DACs/DAC_P0+: C1218.2, C1219.2, R611.2, R612.2; also elsewhere on the board
/DACs/DAC_P45+: C1221.2, R617.2; also elsewhere on the board
/DACs/DAC_P45-: C1222.2, R616.2; also elsewhere on the board
/DACs/DAC_P90+: C1224.2, C1225.2, R620.2, R621.2; also elsewhere on the board
/DACs/DAC_P135+: C1227.2, R626.2; also elsewhere on the board
/DACs/DAC_P135-: C1228.2, R625.2; also elsewhere on the board
/DACs/DAC_P180+: C1231.2, C1232.2, R631.2, R633.2; also elsewhere on the board
/DACs/DAC_P225+: C1237.2, R641.2; also elsewhere on the board
/DACs/DAC_P225-: C1238.2, R639.2; also elsewhere on the board
/DACs/DAC_P270+: C1233.2, C1234.2, R632.2, R634.2; also elsewhere on the board
/DACs/DAC_P315+: C1239.2, R642.2; also elsewhere on the board
/DACs/DAC_P315-: C1240.2, R640.2; also elsewhere on the board
/DACs/TDM1_SDIN_DAC: U601.38 (DSDATA1); also elsewhere on the board
/DACs/VDRIVE: Q601.1, R601.2, U601.24 (VDRIVE)
/SCL0: U601.44 (SCLK/SCL); also elsewhere on the board
/SDA0: U601.43 (MISO/SDA/SA); also elsewhere on the board
unnamed: C627.2, R614.1
unnamed: C1217.1, C1218.1, R607.2
unnamed: C1217.2, C1219.1, R608.2
unnamed: C1220.1, C1221.1, R613.2
unnamed: C1220.2, C1222.1, R615.2
unnamed: C1223.1, C1224.1, R618.2
unnamed: C1223.2, C1225.1, R619.2
unnamed: C1226.1, C1227.1, R622.2
unnamed: C1226.2, C1228.1, R623.2
unnamed: C1229.1, C1231.1, R627.2
unnamed: C1229.2, C1232.1, R628.2
unnamed: C1230.1, C1233.1, R629.2
unnamed: C1230.2, C1234.1, R630.2
unnamed: C1235.1, C1237.1, R635.2
unnamed: C1235.2, C1238.1, R636.2
unnamed: C1236.1, C1239.1, R637.2
unnamed: C1236.2, C1240.1, R638.2
unnamed: C1241.1, C1243.1, R643.2
unnamed: C1242.1, C1244.1, R644.2
unnamed: C1245.1, C1246.1, R645.2
unnamed: C1247.1, C1248.1, R646.2
unnamed: C631.1, C634.1, U601.62 (CM), U602.3 (+)
unnamed: C601.1, U601.59 (DAC_BIAS1)
unnamed: C602.1, U601.60 (DAC_BIAS2)
unnamed: C603.1, U601.1 (DAC_BIAS3)
unnamed: C606.1, U601.2 (DAC_BIAS4)
unnamed: C627.1, C630.1, U601.15 (LF)
unnamed: R602.2, U601.17 (MCLKI/XTALI)
unnamed: C629.1, C633.1, U601.63 (TS_REF)

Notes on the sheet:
make 1%
check jumpers
DAC_Out_9x to 12x go to a header on the top sheet
ADAU 1962 EVAL Board

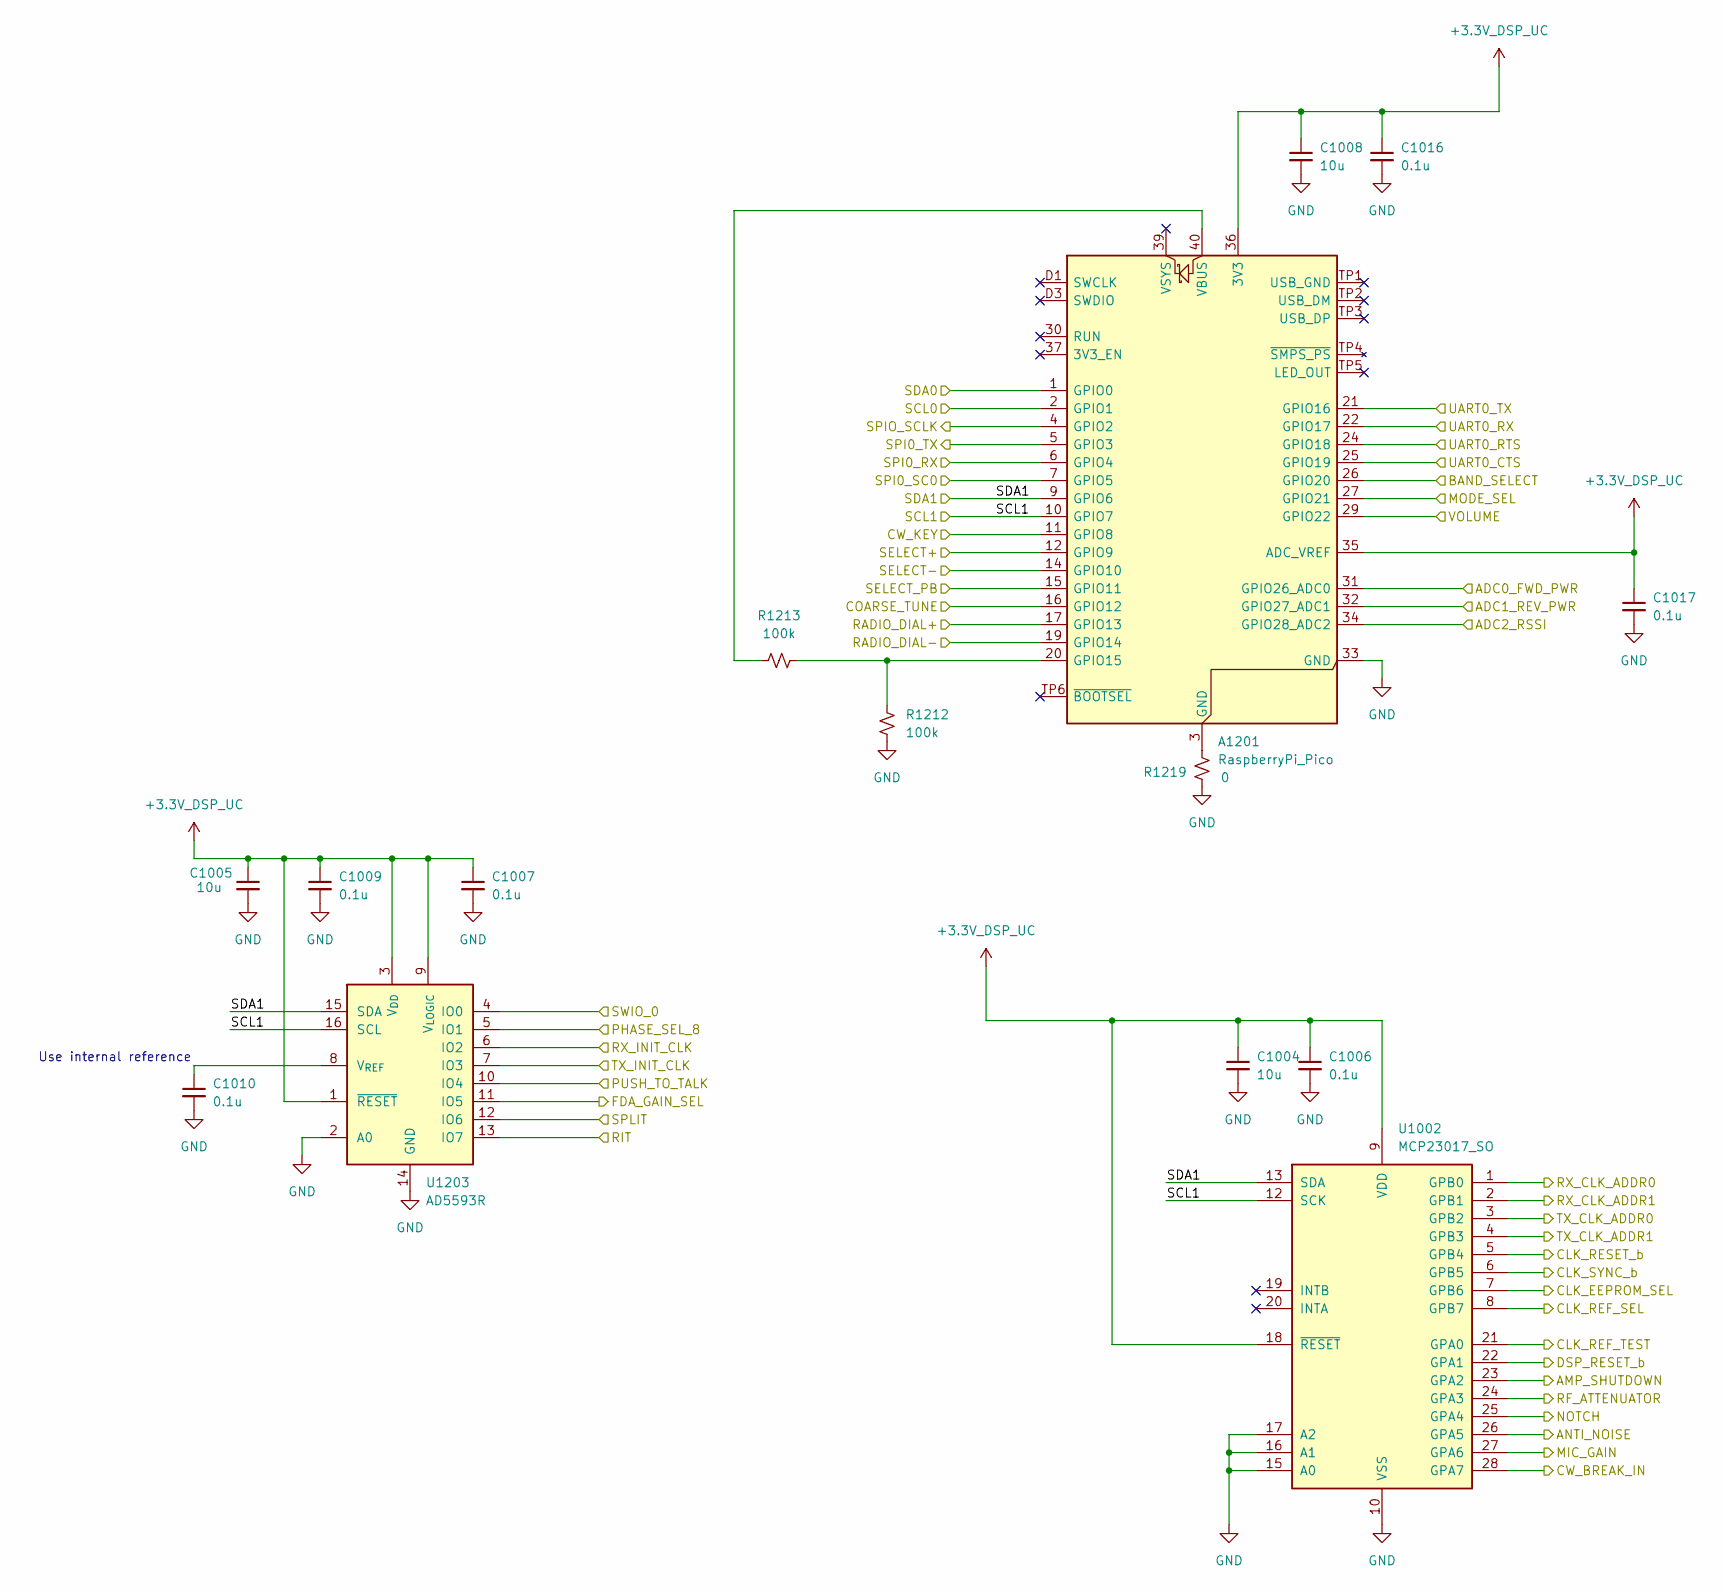
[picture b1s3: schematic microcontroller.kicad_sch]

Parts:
A1201: RaspberryPi_Pico; RaspberryPi_Pico_SMD
C1004, C1005, C1008: 10u; C_0402_1005Metric_Pad0.74x0.62mm_HandSolder
C1006, C1007, C1009, C1010, C1016, C1017: 0.1u; C_0402_1005Metric_Pad0.74x0.62mm_HandSolder
R1212, R1213: 100k; R_0402_1005Metric_Pad0.72x0.64mm_HandSolder
R1219: 0; R_0402_1005Metric_Pad0.72x0.64mm_HandSolder
U1002: MCP23017_SO; SOIC-28W_7.5x17.9mm_P1.27mm
U1203: AD5593R; TSSOP-16_4.4x5mm_P0.65mm

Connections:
+3.3V_DSP_UC: A1201.35 (ADC_VREF), A1201.36 (3V3), C1004.1, C1005.1, C1006.1, C1007.1, C1008.1, C1009.1, C1016.1, C1017.1, U1002.9 (VDD), U1002.18 (~RESET), U1203.1 (~RESET), U1203.3 (V_{DD}), U1203.9 (V_{LOGIC}); also elsewhere on the board
/ADC0_FWD_PWR: A1201.31 (GPIO26_ADC0); also elsewhere on the board
/ADC1_REV_PWR: A1201.32 (GPIO27_ADC1); also elsewhere on the board
/ADC2_RSSI: A1201.34 (GPIO28_ADC2); also elsewhere on the board
/AMP_SHUTDOWN: U1002.23 (GPA2); also elsewhere on the board
/ANTI_NOISE: U1002.26 (GPA5); also elsewhere on the board
/BAND_SELECT: A1201.26 (GPIO20); also elsewhere on the board
/CLK_EEPROM_SEL: U1002.7 (GPB6); also elsewhere on the board
/CLK_REF_SEL: U1002.8 (GPB7); also elsewhere on the board
/CLK_REF_TEST: U1002.21 (GPA0); also elsewhere on the board
/CLK_RESET_b: U1002.5 (GPB4); also elsewhere on the board
/CLK_SYNC_b: U1002.6 (GPB5); also elsewhere on the board
/COARSE_TUNE: A1201.16 (GPIO12); also elsewhere on the board
/CW_BREAK_IN: U1002.28 (GPA7); also elsewhere on the board
/CW_KEY: A1201.11 (GPIO8); also elsewhere on the board
/DSP_RESET_b: U1002.22 (GPA1); also elsewhere on the board
/FDA_GAIN_SEL: U1203.11 (IO5); also elsewhere on the board
/MIC_GAIN: U1002.27 (GPA6); also elsewhere on the board
/MODE_SEL: A1201.27 (GPIO21); also elsewhere on the board
/NOTCH: U1002.25 (GPA4); also elsewhere on the board
/PHASE_SEL_8: U1203.5 (IO1); also elsewhere on the board
/PUSH_TO_TALK: U1203.10 (IO4); also elsewhere on the board
/RADIO_DIAL+: A1201.17 (GPIO13); also elsewhere on the board
/RADIO_DIAL-: A1201.19 (GPIO14); also elsewhere on the board
/RF_ATTENUATOR: U1002.24 (GPA3); also elsewhere on the board
/RIT: U1203.13 (IO7); also elsewhere on the board
/RX_CLK_ADDR0: U1002.1 (GPB0); also elsewhere on the board
/RX_CLK_ADDR1: U1002.2 (GPB1); also elsewhere on the board
/RX_INIT_CLK: U1203.6 (IO2); also elsewhere on the board
/SCL0: A1201.2 (GPIO1); also elsewhere on the board
/SCL1: A1201.10 (GPIO7), U1002.12 (SCK), U1203.16 (SCL); also elsewhere on the board
/SDA0: A1201.1 (GPIO0); also elsewhere on the board
/SDA1: A1201.9 (GPIO6), U1002.13 (SDA), U1203.15 (SDA); also elsewhere on the board
/SELECT+: A1201.12 (GPIO9); also elsewhere on the board
/SELECT-: A1201.14 (GPIO10); also elsewhere on the board
/SELECT_PB: A1201.15 (GPIO11); also elsewhere on the board
/SPI0_RX: A1201.6 (GPIO4); also elsewhere on the board
/SPI0_SC0: A1201.7 (GPIO5); also elsewhere on the board
/SPI0_TX: A1201.5 (GPIO3); also elsewhere on the board
/SPIO_SCLK: A1201.4 (GPIO2); also elsewhere on the board
/SPLIT: U1203.12 (IO6); also elsewhere on the board
/SWIO_0: U1203.4 (IO0); also elsewhere on the board
/TX_CLK_ADDR0: U1002.3 (GPB2); also elsewhere on the board
/TX_CLK_ADDR1: U1002.4 (GPB3); also elsewhere on the board
/TX_INIT_CLK: U1203.7 (IO3); also elsewhere on the board
/UART0_CTS: A1201.25 (GPIO19); also elsewhere on the board
/UART0_RTS: A1201.24 (GPIO18); also elsewhere on the board
/UART0_RX: A1201.22 (GPIO17); also elsewhere on the board
/UART0_TX: A1201.21 (GPIO16); also elsewhere on the board
/VOLUME: A1201.29 (GPIO22); also elsewhere on the board
unnamed: A1201.3 (GND), A1201.8 (GND), A1201.13 (GND), A1201.18 (GND), A1201.23 (GND), A1201.28 (GND), A1201.38 (GND), A1201.D2 (GND), R1219.1
unnamed: A1201.20 (GPIO15), R1212.1, R1213.2
unnamed: A1201.40 (VBUS), R1213.1
unnamed: C1010.1, U1203.8 (V_{REF})

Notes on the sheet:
Use internal reference

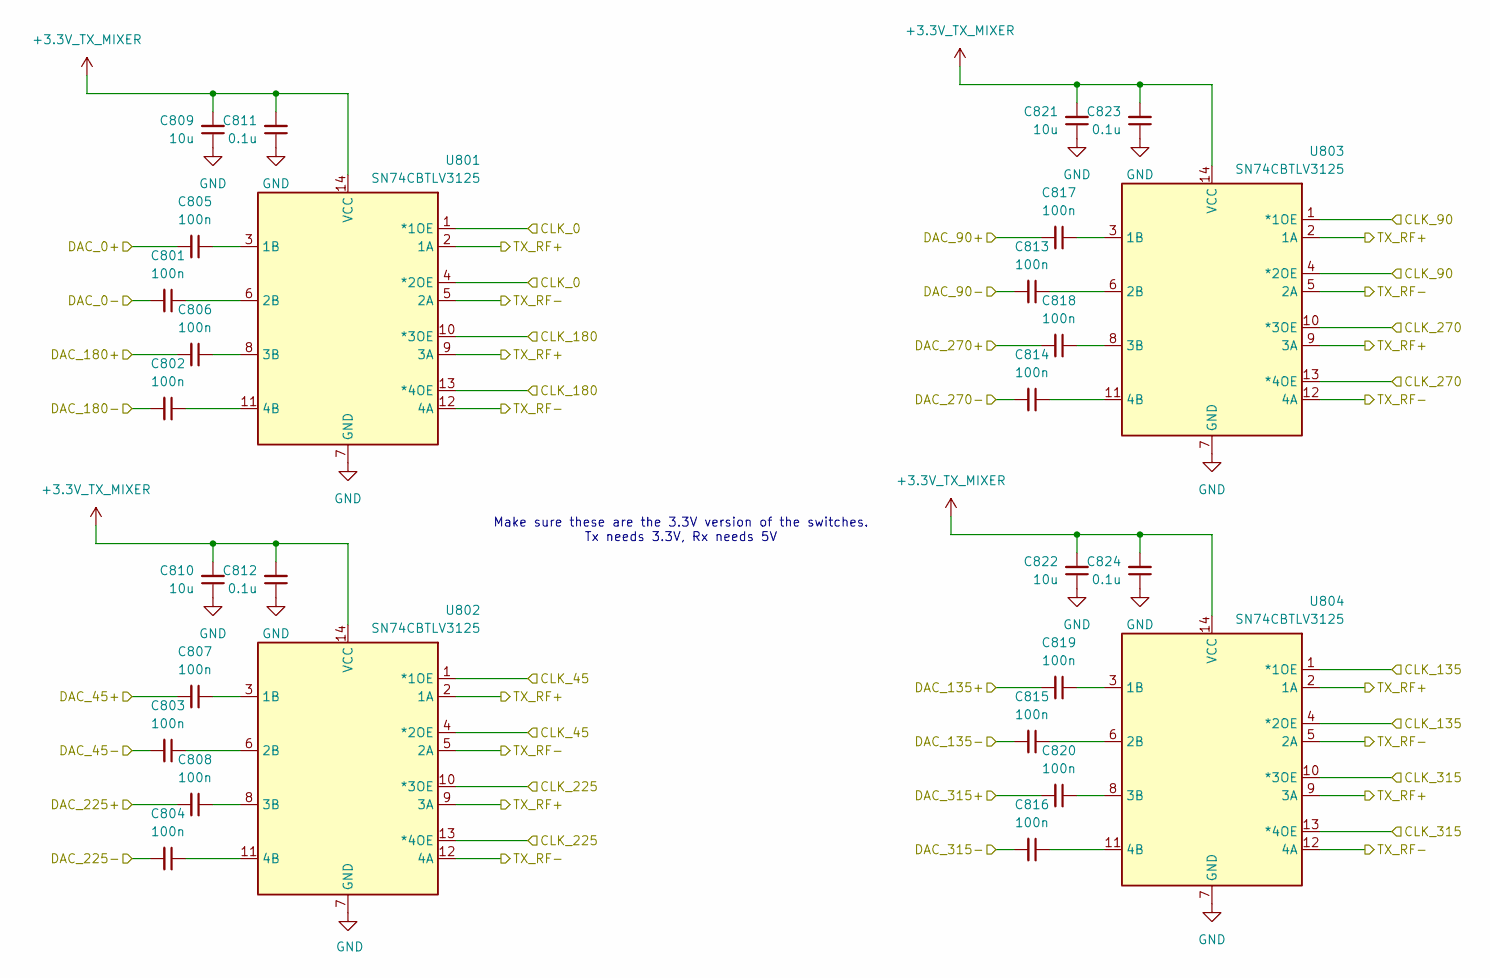
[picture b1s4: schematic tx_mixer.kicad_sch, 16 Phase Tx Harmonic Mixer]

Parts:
C801, C802, C803, C804, C805, C806, C807, C808, C813, C814, C815, C816, C817, C818, C819, C820: 100n; C_0402_1005Metric_Pad0.74x0.62mm_HandSolder
C809, C810, C821, C822: 10u; C_0402_1005Metric_Pad0.74x0.62mm_HandSolder; Digikey Part # 587-3258-1-ND
C811, C812, C823, C824: 0.1u; C_0402_1005Metric_Pad0.74x0.62mm_HandSolder; Digikey Part # 490-GCM31C5C1H104FA16LCT-ND
U801, U802, U803, U804: SN74CBTLV3125; TSSOP-14-1EP_4.4x5mm_P0.65mm

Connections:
+3.3V_TX_MIXER: C809.2, C810.2, C811.2, C812.2, C821.2, C822.2, C823.2, C824.2, U801.14 (VCC), U802.14 (VCC), U803.14 (VCC), U804.14 (VCC); also elsewhere on the board
/Clock_Tree/tx_phase_0: U801.1 (*1OE), U801.4 (*2OE); also elsewhere on the board
/Clock_Tree/tx_phase_45: U802.1 (*1OE), U802.4 (*2OE); also elsewhere on the board
/Clock_Tree/tx_phase_90: U803.1 (*1OE), U803.4 (*2OE); also elsewhere on the board
/Clock_Tree/tx_phase_135: U801.10 (*3OE), U801.13 (*4OE); also elsewhere on the board
/Clock_Tree/tx_phase_180: U804.1 (*1OE), U804.4 (*2OE); also elsewhere on the board
/Clock_Tree/tx_phase_225: U802.10 (*3OE), U802.13 (*4OE); also elsewhere on the board
/Clock_Tree/tx_phase_270: U803.10 (*3OE), U803.13 (*4OE); also elsewhere on the board
/Clock_Tree/tx_phase_315: U804.10 (*3OE), U804.13 (*4OE); also elsewhere on the board
/DACs/DAC_P0+: C801.2, C805.2; also elsewhere on the board
/DACs/DAC_P45+: C807.2; also elsewhere on the board
/DACs/DAC_P45-: C803.2; also elsewhere on the board
/DACs/DAC_P90+: C813.2, C817.2; also elsewhere on the board
/DACs/DAC_P135+: C819.2; also elsewhere on the board
/DACs/DAC_P135-: C815.2; also elsewhere on the board
/DACs/DAC_P180+: C802.2, C806.2; also elsewhere on the board
/DACs/DAC_P225+: C808.2; also elsewhere on the board
/DACs/DAC_P225-: C804.2; also elsewhere on the board
/DACs/DAC_P270+: C814.2, C818.2; also elsewhere on the board
/DACs/DAC_P315+: C820.2; also elsewhere on the board
/DACs/DAC_P315-: C816.2; also elsewhere on the board
/Tx_mixer/TX_RF+: U801.2 (1A), U801.9 (3A), U802.2 (1A), U802.9 (3A), U803.2 (1A), U803.9 (3A), U804.2 (1A), U804.9 (3A); also elsewhere on the board
/Tx_mixer/TX_RF-: U801.5 (2A), U801.12 (4A), U802.5 (2A), U802.12 (4A), U803.5 (2A), U803.12 (4A), U804.5 (2A), U804.12 (4A); also elsewhere on the board
unnamed: C805.1, U801.3 (1B)
unnamed: C801.1, U801.6 (2B)
unnamed: C806.1, U801.8 (3B)
unnamed: C802.1, U801.11 (4B)
unnamed: C807.1, U802.3 (1B)
unnamed: C803.1, U802.6 (2B)
unnamed: C808.1, U802.8 (3B)
unnamed: C804.1, U802.11 (4B)
unnamed: C817.1, U803.3 (1B)
unnamed: C813.1, U803.6 (2B)
unnamed: C818.1, U803.8 (3B)
unnamed: C814.1, U803.11 (4B)
unnamed: C819.1, U804.3 (1B)
unnamed: C815.1, U804.6 (2B)
unnamed: C820.1, U804.8 (3B)
unnamed: C816.1, U804.11 (4B)

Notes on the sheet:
Make sure these are the 3.3V version of the switches. Tx needs 3.3V, Rx needs 5V
